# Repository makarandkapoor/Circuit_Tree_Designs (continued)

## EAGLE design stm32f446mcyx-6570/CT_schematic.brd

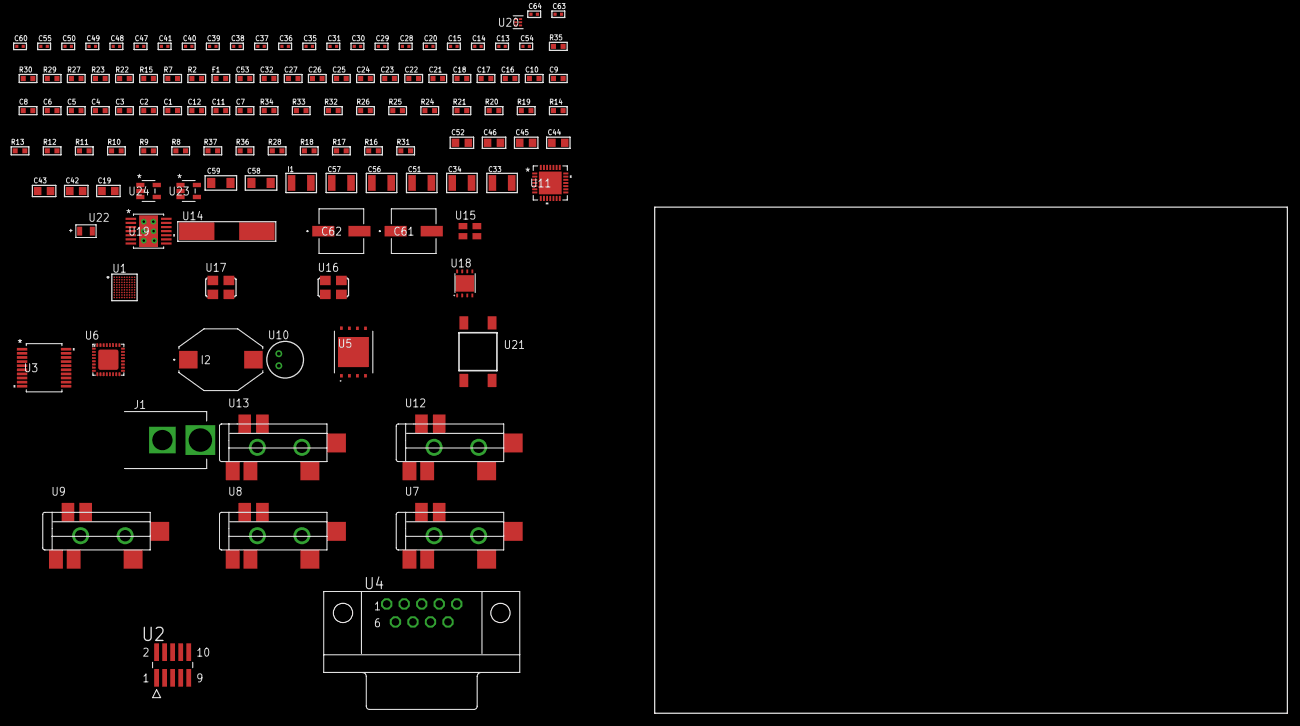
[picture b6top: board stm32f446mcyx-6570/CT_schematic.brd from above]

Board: 2 copper layers, 100.0 x 80.0 mm, 124 parts (0 on the bottom side), 80 nets, no tracks yet.

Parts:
C1, C9, C16, C17, C18, C21, C22, C23, C24, C25, C26, C27, C32, C53: 1e-06; C0603
C2, C3, C4, C5, C6, C10: 1e-07; C0603
C7: 4.7e-06; C0603
C8: 1e-08; C0603
C11, C12: 2.2e-06; C0603
C13, C14: 1e-11; C0402
C15, C28, C29, C30, C31, C37, C38, C39, C40, C41, C55, C60: 1e-07; C0402
C19: 4.7e-06; C0805
C20, C47, C48, C49, C50, C63, C64: 1e-08; C0402
C33, C34, C56, C57: 2.2e-05; C1210
C35, C36: 1e-09; C0402
C42, C43, C44, C45, C46, C52: 1e-05; C0805
C51: 1e-05; C1210
C54: 3.3e-09; C0402
C58, C59: 1e-05; C1206
C61, C62: 0.0001; EXV-9H
F1: 240.0; L0603
I1: 1.5e-05; L1210
I2: 1e-05; IND_PM3316
J1: PJ-037B; PJ-037B_PACKAGE
R2, R30: 1000.0; R0603
R7: 4700.0; R0603
R8, R9, R10, R11, R12, R13, R14, R19, R20, R21, R33, R34: 10000.0; R0603
R15: 5.0; R0603
R16, R17, R18, R28: 100000.0; R0603
R22, R23: 1270.0; R0603
R24, R25, R26: 47000.0; R0603
R27: 680.0; R0603
R29: 200.0; R0603
R31: 71007.101651032; R0603
R32: 22000.0; R0603
R35: 9100.0; R0603
R36: 680000.0; R0603
R37: 120000.0; R0603
U1: STM32F446MCY6; WLCSP81
U2: FTSH-105-01-L-DV-K; SAMTEC_FTSH-105-01-L-DV-K
U3: MAX3218EAP+T; SSOP-20
U4: 182-009-113R531; 182-009-MALE
U5: S25FL128SDPNFI001; WNG008
U6: SGTL5000XNAA3; QFN-32
U7, U8, U9, U12, U13: SJ-43515TS-SMT-TR
U10: WM-64PCT; WM-64PC
U11: WM8731CLSEFL; QFN-28
U14: ABLS-25.000MHZ-B2F-T
U15: ASEK-32.768KHz-ECST; ASEK
U16: ASFL1-12.288MHZ-EC-T; ASFL1
U17: ASFL-24.57MHZ-NCS; ASFL1
U18: LP3878SDX-ADJ/NOPB; WSON-8
U19: tps54225PWP; HTSSOP14
U20: TPS3895ADRYR; SON-6
U21: 4-1437565-2; SW_4-1437565-2
U22: Q65110A2395; LGM67K-G1J2-24-Z
U23, U24: nc7sz125m5x; NC7SZ125M5X

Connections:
CLK_CRYSTAL_U1_E9: C13.1, U1.E9, U14.1
CLK_CRYSTAL_U1_F9: C14.1, U1.F9, U14.2
CLK_U1_C9: U1.C9, U15.3
CLK_U6_21: U6.21, U17.3
CLK_U11_1: U11.1, U16.3
GND: C1.2, C2.2, C3.2, C4.2, C5.2, C6.2, C7.2, C8.2, C9.2, C10.2, C11.2, C12.2, C13.2, C14.2, C15.2, C16.2, C17.2, C18.2, C20.2, C28.2, C29.2, C30.2, C31.2, C32.2, C36.2, C37.2, C38.2, C39.2, C40.2, C41.2, C42.2, C43.2, C44.2, C45.2, C46.2, C47.2, C48.2, C49.2, C50.2, C51.2, C52.2, C53.2, C54.2, C56.2, C57.2, C58.2, C59.2, C60.2, C61.2, C62.2, C63.2, C64.2, J1.2, R2.2, R8.2, R10.2, R14.2, R15.2, R23.2, R24.2, R25.2, R26.2, R30.2, R32.2, R35.2, R37.2, U1.B1, U1.B7, U1.F7, U1.G8, U1.H3, U2.3, U2.5, U3.5, U3.17, U3.20, U4.5, U5.4, U5.PAD, U6.1, U6.3, U6.7, U6.EXP, U8.1, U9.1, U10.2, U11.4, U11.15, U11.19, U11.25, U11.26, U11.29, U12.1, U13.1, U15.2, U16.2, U17.2, U18.3, U18.PAD, U19.5, U19.8, U19.9, U19.15, U20.2, U22.C, U23.2, U23.3, U24.1, U24.3
NET_U1_A7: R8.1, U1.A7
NET_U1_B8: R9.1, U1.B8
NET_U1_C2: C12.1, U1.C2
NET_U1_D8: R7.1, U1.D8, U24.4
NET_U1_H8: C8.1, C9.1, F1.1, U1.H8
NET_U1_J3: C11.1, U1.J3
NET_U1_J8: R10.1, U1.J8
NET_U1_J9: U21.3, U21.4
NET_U2_9: R15.1, U2.9
NET_U3_1: I1.1, U3.1
NET_U3_2: R16.1, U3.2
NET_U3_3: R17.1, U3.3
NET_U3_4: R18.1, U3.4
NET_U3_15: C18.1, U3.15
NET_U3_16: C19.2, U3.16
NET_U3_18: C19.1, U3.18
NET_U3_19: C17.1, U3.19
NET_U4_2: U3.12, U4.2
NET_U4_3: U3.14, U4.3
NET_U4_7: U3.11, U4.7
NET_U4_8: U3.13, U4.8
NET_U5_3: R19.1, U5.3
NET_U5_7: R21.1, U5.7
NET_U6_10: C31.1, U6.10
NET_U6_29: R22.1, U6.29
NET_U6_31: R23.1, U6.31
NET_U7_1: U6.4, U7.1
NET_U7_2: U6.2, U7.2
NET_U7_5: U6.6, U7.5
NET_U8_2: C22.1, U8.2
NET_U8_5: C21.1, U8.5
NET_U9_2: C24.1, C25.1, U9.2
NET_U9_5: C23.1, U9.5
NET_U9_13: C24.2, C25.2
NET_U10_1: C26.1, C27.1, C32.1, U6.16, U10.1
NET_U10_15: C26.2, C27.2
NET_U11_20: C41.1, C46.1, U11.20
NET_U12_2: C34.1, R25.1, U12.2
NET_U12_5: C33.1, R24.1, U12.5
NET_U13_5: C35.1, C36.1, R26.1, R27.1, U13.5
NET_U18_1: C50.1, U18.1
NET_U18_6: R29.2, R30.1, U18.6
NET_U18_8: R28.1, U18.8
NET_U19_2: R31.2, R32.1, U19.2
NET_U19_3: C53.1, U19.3
NET_U19_4: C54.1, U19.4
NET_U19_10: C55.1, I2.1, U19.10, U19.11
NET_U19_12: C55.2, U19.12
NET_U20_1: R34.1, R35.1, U20.1
NET_U20_3: R36.2, R37.1, U20.3
NET_U20_4: R33.1, U20.4, U23.4, U24.2
NET_U21_1: R2.1, U21.1, U21.2
PROC_I2S1_CK: U1.F6, U6.24
PROC_I2S1_SD: U1.A6, U6.26
PROC_I2S1_WS: U1.H7, U6.23
PROC_I2S2_CK: U1.F2, U11.7
PROC_I2S2_SD: U1.F8, U11.8
PROC_I2S2_WS: U1.B5, U11.9, U11.11
PROC_SPI2_MISO: U1.E8, U5.2
PROC_SPI2_MOSI: U1.G3, U5.5
PROC_SPI2_NSS: R20.1, U1.C4, U5.1
PROC_SPI2_SCK: U1.F4, U5.6
PROC_SYS_JTCK_SWCLK: R14.1, U1.C3, U2.4
PROC_SYS_JTDI: R12.1, U1.B2, U2.8
PROC_SYS_JTDO_SWO: U1.A5, U2.6
PROC_SYS_JTMS_SWDIO: R13.1, U1.D2, U2.2
PROC_UART5_CTS: U1.D1, U3.8
PROC_UART5_RTS: U1.F3, U3.10
PROC_UART5_RX: U1.D5, U3.9
PROC_UART5_TX: U1.A2, U3.7
RST_OUT_U2_JTAG_RST_B: R11.1, U2.10, U23.1
VCC_S1_11V7: C51.1, C58.1, C59.1, C61.1, C62.1, J1.1, R28.2, U18.4, U19.7, U19.13, U19.14
VCC_TIER1_1V2: C28.1, C52.1, R29.1, U6.30, U18.5
VCC_TIER1_3V3: C1.1, C2.1, C3.1, C4.1, C5.1, C6.1, C7.1, C10.1, C15.1, C16.1, C20.1, C29.1, C30.1, C37.1, C38.1, C39.1, C40.1, C42.1, C43.1, C44.1, C45.1, C47.1, C48.1, C49.1, C56.1, C57.1, C60.1, C63.1, C64.1, F1.2, I1.2, I2.2, R7.2, R9.2, R11.2, R12.2, R13.2, R16.2, R17.2, R18.2, R19.2, R20.2, R21.2, R22.2, R31.1, R33.2, R34.2, R36.1, U1.A1, U1.A8, U1.B9, U1.E1, U1.H9, U1.J2, U2.1, U3.6, U5.8, U6.5, U6.20, U11.3, U11.5, U11.12, U11.18, U15.4, U16.4, U17.4, U19.1, U20.6, U23.5, U24.5

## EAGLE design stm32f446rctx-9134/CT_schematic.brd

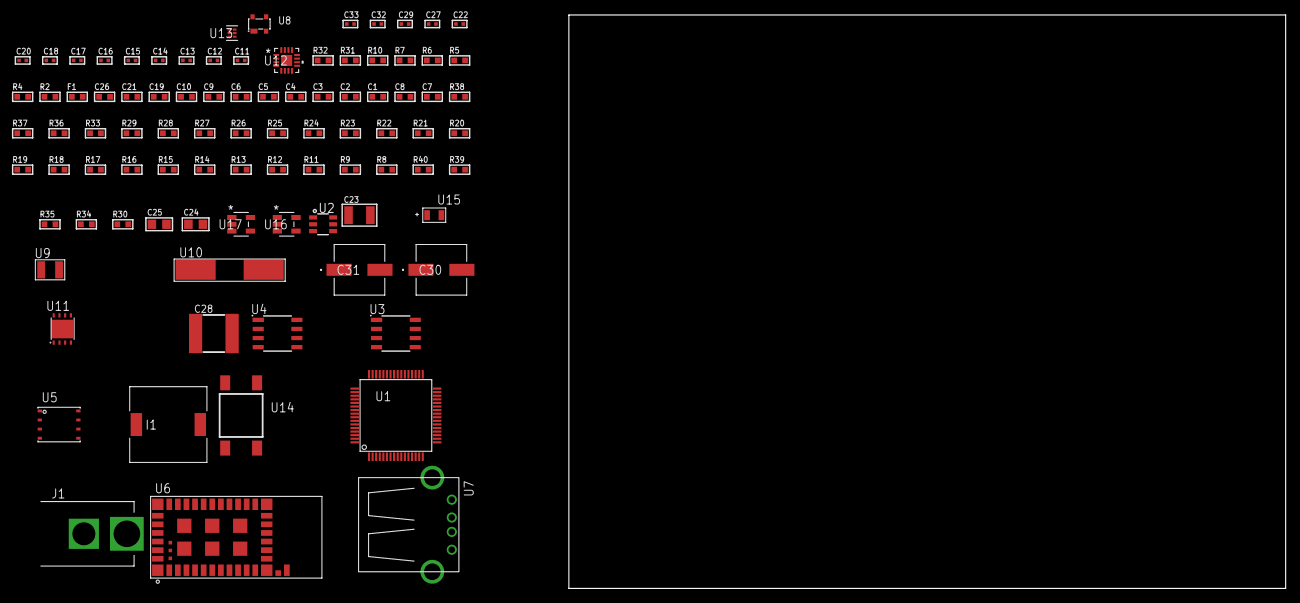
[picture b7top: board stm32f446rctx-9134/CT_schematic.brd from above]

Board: 2 copper layers, 100.0 x 80.0 mm, 91 parts (0 on the bottom side), 59 nets, no tracks yet.

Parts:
C1, C10, C19, C21, C26: 1e-06; C0603
C2, C3, C4, C5, C6: 1e-07; C0603
C7: 4.7e-06; C0603
C8: 2.2e-06; C0603
C9: 1e-08; C0603
C11, C12, C13, C14: 1e-11; C0402
C15, C16, C17, C22, C32, C33: 1e-08; C0402
C18, C20, C27, C29: 1e-07; C0402
C23: 1e-05; C1210
C24, C25: 1e-05; C0805
C28: 6.8e-05; 2220
C30, C31: 0.0001; EXV-9H
F1: 240.0; L0603
I1: 7e-06; DR1040
J1: PJ-037B; PJ-037B_PACKAGE
R2, R32: 1000.0; R0603
R4, R5: 4700.0; R0603
R6, R7: 2200.0; R0603
R8: 47000.0; R0603
R9, R11, R12, R13, R14, R15, R16, R17, R18, R19, R20, R21, R22, R29, R36, R37: 10000.0; R0603
R10: 1270.0; R0603
R23, R24, R25, R26, R27, R28: 34000.0; R0603
R30: 100000.0; R0603
R31: 806.0; R0603
R33: 20000.0; R0603
R34: 150000.0; R0603
R35, R39: 300000.0; R0603
R38: 82000.0; R0603
R40: 120000.0; R0603
U1: STM32F446RCT7; LQFP64
U2: MAX4995AAUT+T; SOT-23-6
U3: AT25010B-SSHL-T; SOIC-8
U4: AT25128B-SSHL-T; SOIC-8
U5: 24AA256-I/MF; DFN8-S
U6: 88-00153-02
U7: 61400416021; USB-A-H
U8: prtr5v0u2ax; SOT143B
U9: ABS07-32.768KHZ-7-T
U10: ABLS-25.000MHZ-B2F-T
U11: LP3878SDX-ADJ/NOPB; WSON-8
U12: LTC3601EUD#PBF; QFN-16_EP
U13: TPS3895ADRYR; SON-6
U14: 4-1437565-2; SW_4-1437565-2
U15: Q65110A2395; LGM67K-G1J2-24-Z
U16, U17: nc7sz125m5x; NC7SZ125M5X

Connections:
CLK_CRYSTAL_U1_3: C11.1, U1.3, U9.1
CLK_CRYSTAL_U1_4: C12.1, U1.4, U9.2
CLK_CRYSTAL_U1_5: C13.1, U1.5, U10.1
CLK_CRYSTAL_U1_6: C14.1, U1.6, U10.2
GND: C1.2, C2.2, C3.2, C4.2, C5.2, C6.2, C7.2, C8.2, C9.2, C10.2, C11.2, C12.2, C13.2, C14.2, C15.2, C16.2, C17.2, C18.2, C19.2, C20.2, C21.2, C22.2, C23.2, C24.2, C25.2, C26.2, C28.1, C28.2, C29.2, C30.2, C31.2, C32.2, C33.2, J1.2, R2.2, R8.2, R9.2, R10.2, R12.2, R20.2, R21.2, R29.2, R32.2, R33.2, R35.2, R38.2, R40.2, U1.12, U1.18, U1.31, U1.47, U1.63, U2.2, U3.4, U4.4, U5.4, U5.7, U6.1, U6.9, U6.13, U6.14, U6.15, U6.16, U6.17, U6.18, U6.19, U6.20, U6.21, U6.22, U6.23, U6.24, U6.25, U6.26, U6.27, U6.31, U6.32, U6.39, U6.40, U6.41, U6.42, U6.43, U6.44, U6.49, U7.4, U7.5, U7.6, U8.1, U11.3, U11.PAD, U12.1, U12.9, U12.17, U13.2, U15.C, U16.1, U16.3, U17.1, U17.3
NET_U1_7: R5.1, U1.7, U17.4
NET_U1_13: C9.1, C10.1, F1.1, U1.13
NET_U1_30: C8.1, U1.30
NET_U1_43: R10.1, U1.43
NET_U1_58: R6.1, U1.58, U5.6
NET_U1_59: R7.1, U1.59, U5.5
NET_U1_60: R9.1, U1.60
NET_U1_62: U14.3, U14.4
NET_U2_3: R8.1, U2.3
NET_U3_3: R13.1, U3.3
NET_U3_7: R15.1, U3.7
NET_U4_3: R16.1, U4.3
NET_U4_7: R18.1, U4.7
NET_U5_1: R19.1, U5.1
NET_U5_2: R20.1, U5.2
NET_U5_3: R21.1, U5.3
NET_U6_6: R29.1, U6.6
NET_U6_10: R4.1, U6.10, U16.4
NET_U6_11: R22.1, U6.11
NET_U11_1: C22.1, U11.1
NET_U11_6: R31.2, R32.1, U11.6
NET_U11_8: R30.1, U11.8
NET_U12_3: C27.2, I1.1, U12.3, U12.4
NET_U12_6: C27.1, U12.6
NET_U12_7: C26.1, U12.7, U12.12
NET_U12_10: R35.1, U12.10
NET_U12_11: R33.1, R34.1, U12.11
NET_U12_ATNET_3: I1.2, R34.2
NET_U13_1: R37.1, R38.1, U13.1
NET_U13_3: R39.2, R40.1, U13.3
NET_U13_4: R36.1, U13.4, U16.2, U17.2
NET_U14_1: R2.1, U14.1, U14.2
PROC_GPIO_TO_U1_USB_FAULT: R11.1, U1.8, U2.6
PROC_GPIO_TO_U1_VBUS_EN: R12.1, U1.2, U2.4
PROC_SDIO_CK: R28.1, U1.28, U6.36
PROC_SDIO_CMD: R27.1, U1.54, U6.37
PROC_SDIO_D0: R23.1, U1.39, U6.35
PROC_SDIO_D1: R24.1, U1.26, U6.34
PROC_SDIO_D2: R25.1, U1.27, U6.2
PROC_SDIO_D3: R26.1, U1.52, U6.38
PROC_SPI1_MISO: U1.22, U4.2
PROC_SPI1_MOSI: U1.23, U4.5
PROC_SPI1_NSS: R17.1, U1.20, U4.1
PROC_SPI1_SCK: U1.21, U4.6
PROC_SPI2_MISO: U1.10, U3.2
PROC_SPI2_MOSI: U1.9, U3.5
PROC_SPI2_NSS: R14.1, U1.33, U3.1
PROC_SPI2_SCK: U1.29, U3.6
PROC_USB_OTG_FS_DM: U1.44, U7.2, U8.3
PROC_USB_OTG_FS_DP: U1.45, U7.3, U8.2
PROC_USB_OTG_FS_VBUS: U1.42, U2.1, U7.1, U8.4
VCC_S1_12V3: C23.1, C25.1, C30.1, C31.1, J1.1, R30.2, U11.4, U12.15, U12.16
VCC_TIER1_1V8: C1.1, C2.1, C3.1, C4.1, C5.1, C6.1, C7.1, C15.1, C16.1, C17.1, C20.1, C21.1, C24.1, C29.1, C32.1, C33.1, F1.2, R4.2, R5.2, R6.2, R7.2, R11.2, R13.2, R14.2, R15.2, R16.2, R17.2, R18.2, R19.2, R22.2, R23.2, R24.2, R25.2, R26.2, R27.2, R28.2, R31.1, R36.2, R37.2, R39.1, U1.1, U1.19, U1.32, U1.48, U1.64, U3.8, U4.8, U5.8, U6.33, U11.5, U13.6, U16.5, U17.5
VCC_TIER1_5V0: C18.1, C19.1, C28.2, I1.2, R34.2, U2.5, U6.12, U12.8

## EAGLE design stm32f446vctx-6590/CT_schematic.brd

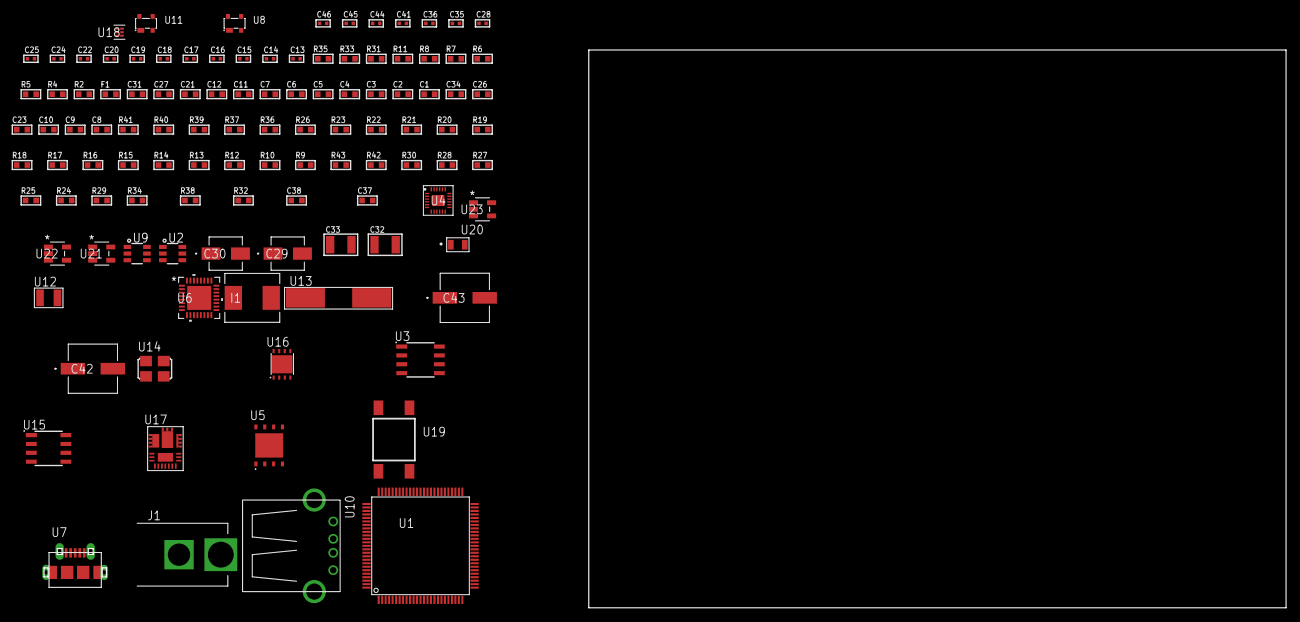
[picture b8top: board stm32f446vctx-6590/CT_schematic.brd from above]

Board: 2 copper layers, 178.1 x 80.0 mm, 111 parts (0 on the bottom side), 84 nets, no tracks yet.

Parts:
C1, C12, C21, C27: 1e-06; C0603
C2, C3, C4, C5, C6, C7: 1e-07; C0603
C8: 4.7e-06; C0603
C9, C10, C23, C26, C34: 2.2e-06; C0603
C11: 1e-08; C0603
C13, C14, C15, C16: 1e-11; C0402
C17, C20, C28, C44, C45, C46: 1e-08; C0402
C18, C19, C22, C24, C25, C35, C36, C41: 1e-07; C0402
C29: 1e-06; EXV-9B
C30: 2.2e-06; EXV-9B
C31: 8e-07; R0603
C32: 1e-05; C1210
C33: 0.0001; C1210
C37: 8.7488758840791e-09; R0603
C38: 2.9825713241179e-07; R0603
C42, C43: 0.0001; EXV-9H
F1: 240.0; L0603
I1: 6.8e-07; IND25X25CZ
J1: PJ-037B; PJ-037B_PACKAGE
R2: 1000.0; R0603
R4, R5, R6: 4700.0; R0603
R7, R8: 2200.0; R0603
R9, R21, R26: 47000.0; R0603
R10, R12, R13, R14, R15, R16, R17, R18, R19, R20, R22, R23, R39, R40: 10000.0; R0603
R11: 1270.0; R0603
R24, R25, R27, R28, R30: 100000.0; R0603
R29: 153694.38; R0603
R31: 0.1; R0603
R32: 4030.2416170974; R0603
R33: 453.0; R0603
R34: 58.26650887574; R0603
R35: 130.0; R0603
R36: 39000.0; R0603
R37: 49900.0; R0603
R38: 5113.9346405229; R0603
R41: 82000.0; R0603
R42: 300000.0; R0603
R43: 120000.0; R0603
U1: STM32F446VCT6; LQFP100
U2, U9: MAX4995AAUT+T; SOT-23-6
U3: AT25128B-SSHL-T; SOIC-8
U4: MPU-9250; QFN24_2
U5: MX25R6435FZAIH0; WSON-8-PAD
U6: TUSB1210BRHBR; RHB32_3P45X3P45
U7: 47590-0001; MICRO_USB_AB
U8, U11: prtr5v0u2ax; SOT143B
U10: 61400416021; USB-A-H
U12: ABS07-32.768KHZ-7-T
U13: ABLS-25.000MHZ-B2F-T
U14: ASFL1-19.2MHZ-NCS; ASFL1
U15: LP2954AIMX/NOPB; LP2954
U16: LP2951ACSDX/NOPB; WSON-8
U17: IR3899MTR1PBF
U18: TPS3895ADRYR; SON-6
U19: 4-1437565-2; SW_4-1437565-2
U20: Q65110A2395; LGM67K-G1J2-24-Z
U21, U22, U23: nc7sz125m5x; NC7SZ125M5X

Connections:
CLK_CRYSTAL_U1_8: C13.1, U1.8, U12.1
CLK_CRYSTAL_U1_9: C14.1, U1.9, U12.2
CLK_CRYSTAL_U1_12: C15.1, U1.12, U13.1
CLK_CRYSTAL_U1_13: C16.1, U1.13, U13.2
CLK_U6_1: U6.1, U14.3
GND: C1.2, C2.2, C3.2, C4.2, C5.2, C6.2, C7.2, C8.2, C9.2, C10.2, C11.2, C12.2, C13.2, C14.2, C15.2, C16.2, C17.2, C18.2, C19.2, C20.2, C21.2, C22.2, C23.2, C24.2, C25.2, C26.2, C27.2, C28.2, C29.2, C30.2, C31.2, C32.2, C34.2, C35.2, C36.2, C41.2, C42.2, C43.2, C44.2, C45.2, C46.2, J1.2, R2.2, R9.2, R10.2, R11.2, R13.2, R21.2, R23.2, R27.2, R30.2, R31.1, R31.2, R33.2, R36.2, R38.2, R41.2, R43.2, U1.10, U1.20, U1.27, U1.49, U1.74, U1.99, U2.2, U3.4, U4.18, U4.20, U4.25, U5.4, U5.PAD, U6.33, U7.5, U7.6, U7.7, U7.8, U7.9, U8.1, U9.2, U10.4, U10.5, U10.6, U11.1, U14.2, U15.4, U16.3, U16.4, U16.PAD, U17.4, U17.11, U17.17, U18.2, U20.C, U21.1, U21.3, U22.1, U22.3, U23.1, U23.3
NET_U1_14: R5.1, U1.14, U22.4
NET_U1_22: C11.1, C12.1, F1.1, U1.21, U1.22
NET_U1_48: C9.1, U1.48
NET_U1_69: R11.1, U1.69
NET_U1_73: C10.1, U1.73
NET_U1_93: R8.1, U1.93, U4.24
NET_U1_94: R10.1, U1.94
NET_U1_95: R7.1, U1.95, U4.23
NET_U1_98: U19.3, U19.4
NET_U2_3: R9.1, U2.3
NET_U3_3: R14.1, U3.3
NET_U3_7: R16.1, U3.7
NET_U4_9: R18.1, U4.9
NET_U4_10: C18.1, U4.10
NET_U4_22: R17.1, U4.22
NET_U5_7: R4.1, U1.24, U5.7, U21.4
NET_U6_11: R22.1, U6.11
NET_U6_12: C26.1, U6.12
NET_U6_14: R23.1, U6.14
NET_U6_20: C23.1, U6.20
NET_U6_27: R6.1, U6.27, U23.4
NET_U7_1: C27.1, U6.22, U7.1, U8.4, U9.1
NET_U7_2: U6.19, U7.2, U8.3
NET_U7_3: U6.18, U7.3, U8.2
NET_U7_4: U6.23, U7.4
NET_U9_3: R21.1, U9.3
NET_U9_4: U6.17, U9.4
NET_U15_3: R25.1, U15.3
NET_U15_5: R24.1, U15.5
NET_U15_7: R26.2, R27.1, U15.7
NET_U16_5: R28.1, U16.5
NET_U16_7: R29.2, R30.1, U16.7
NET_U17_1: C37.1, R32.1, R33.1, R34.1, R35.1, U17.1, U17.8
NET_U17_2: C36.1, U17.2
NET_U17_3: C37.2, C38.1, C38.2, U17.3
NET_U17_5: R36.1, U17.5
NET_U17_10: C34.1, U17.10
NET_U17_12: C33.1, I1.1, U17.12
NET_U17_14: C33.2, U17.14
NET_U17_15: R37.1, R38.1, U17.15
NET_U17_ATNET_3: I1.2, R32.2
NET_U17_ATNET_4: C38.2, R34.2
NET_U18_1: R40.1, R41.1, U18.1
NET_U18_3: R42.2, R43.1, U18.3
NET_U18_4: R39.1, U18.4, U21.2, U22.2, U23.2
NET_U19_1: R2.1, U19.1, U19.2
PROC_GPIO_TO_U1_USB_FAULT: R12.1, U1.3, U2.6
PROC_GPIO_TO_U1_VBUS_EN: R13.1, U1.2, U2.4
PROC_GPIO_TO_U4_FSYNC: U1.5, U4.11
PROC_GPIO_TO_U4_INT_B: U1.4, U4.12
PROC_QUADSPI_BK1_IO0: U1.58, U5.5
PROC_QUADSPI_BK1_IO1: U1.59, U5.2
PROC_QUADSPI_BK1_IO2: R20.1, U1.1, U5.3
PROC_QUADSPI_BK1_NCS: R19.1, U1.92, U5.1
PROC_QUADSPI_CLK: U1.84, U5.6
PROC_SPI1_MISO: U1.31, U3.2
PROC_SPI1_MOSI: U1.32, U3.5
PROC_SPI1_NSS: R15.1, U1.29, U3.1
PROC_SPI1_SCK: U1.89, U3.6
PROC_USB_OTG_FS_DM: U1.70, U10.2, U11.3
PROC_USB_OTG_FS_DP: U1.71, U10.3, U11.2
PROC_USB_OTG_FS_VBUS: U1.68, U2.1, U10.1, U11.4
PROC_USB_OTG_HS_ULPI_CK: U1.30, U6.26
PROC_USB_OTG_HS_ULPI_D0: U1.26, U6.3
PROC_USB_OTG_HS_ULPI_D1: U1.35, U6.4
PROC_USB_OTG_HS_ULPI_D2: U1.36, U6.5
PROC_USB_OTG_HS_ULPI_D3: U1.47, U6.6
PROC_USB_OTG_HS_ULPI_D4: U1.37, U6.7
PROC_USB_OTG_HS_ULPI_D5: U1.51, U6.9
PROC_USB_OTG_HS_ULPI_D6: U1.52, U6.10
PROC_USB_OTG_HS_ULPI_D7: U1.91, U6.13
PROC_USB_OTG_HS_ULPI_DIR: U1.17, U6.31
PROC_USB_OTG_HS_ULPI_NXT: U1.18, U6.2
PROC_USB_OTG_HS_ULPI_STP: U1.15, U6.29
VCC_S1_16V9: C29.1, C31.1, C35.1, C42.1, C43.1, J1.1, R25.2, R37.2, U15.8, U16.8, U17.9
VCC_TIER1_1V8: C1.1, C2.1, C3.1, C4.1, C5.1, C6.1, C7.1, C8.1, C17.1, C20.1, C21.1, C24.1, C25.1, C30.1, C41.1, C44.1, C45.1, C46.1, F1.2, R4.2, R5.2, R6.2, R7.2, R8.2, R12.2, R14.2, R15.2, R16.2, R17.2, R18.2, R19.2, R20.2, R22.2, R24.2, R26.1, R39.2, R40.2, R42.1, U1.6, U1.11, U1.19, U1.28, U1.50, U1.75, U1.100, U3.8, U4.1, U4.8, U5.8, U6.28, U6.30, U6.32, U15.1, U18.6, U21.5, U22.5, U23.5
VCC_TIER1_3V3: C19.1, C22.1, C28.1, C32.1, R28.2, R29.1, U4.13, U6.21, U14.4, U16.1
VCC_TIER1_5V0: I1.2, R32.2, U2.5, U9.5
